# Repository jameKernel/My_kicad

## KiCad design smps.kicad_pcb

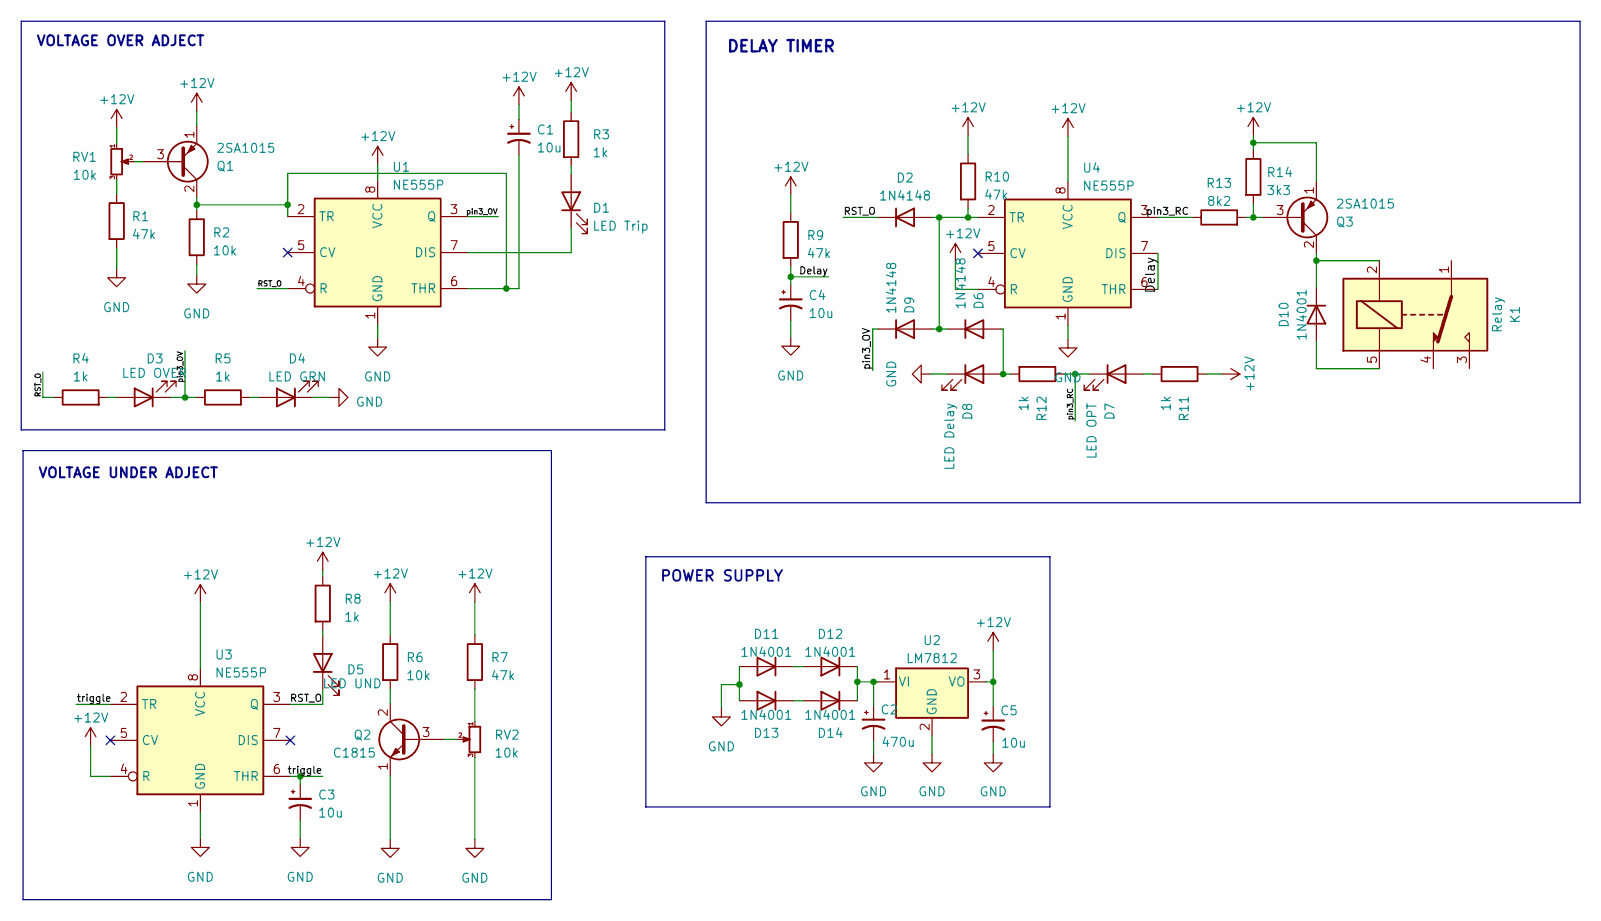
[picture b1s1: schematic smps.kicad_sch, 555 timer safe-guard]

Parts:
C1, C3, C5: 10u; CP_Radial_D4.0mm_P2.00mm
C2: 470u; CP_Radial_D6.3mm_P2.50mm
C4: 10u; CP_Radial_D6.3mm_P2.50mm
D1: LED Trip; LED_Rectangular_W5.0mm_H2.0mm
D2, D6, D9: 1N4148; D_DO-35_SOD27_P7.62mm_Horizontal
D3: LED OVER; LED_Rectangular_W5.0mm_H2.0mm
D4: LED GRN; LED_Rectangular_W5.0mm_H2.0mm
D5: LED UND; LED_Rectangular_W5.0mm_H2.0mm
D7: LED OPT; LED_Rectangular_W5.0mm_H2.0mm
D8: LED Delay; LED_Rectangular_W5.0mm_H2.0mm
D10, D11, D12, D13, D14: 1N4001; D_DO-41_SOD81_P10.16mm_Horizontal
K1: Relay; Relay_SPDT_SANYOU_SRD_Series_Form_C
Q1, Q3: 2SA1015; TO-92_Inline
Q2: C1815; TO-92_Inline
R1, R7, R9, R10: 47k; R_Axial_DIN0207_L6.3mm_D2.5mm_P10.16mm_Horizontal
R2, R6: 10k; R_Axial_DIN0207_L6.3mm_D2.5mm_P10.16mm_Horizontal
R3, R4, R5, R8, R11, R12: 1k; R_Axial_DIN0207_L6.3mm_D2.5mm_P10.16mm_Horizontal
R13: 8k2; R_Axial_DIN0207_L6.3mm_D2.5mm_P10.16mm_Horizontal
R14: 3k3; R_Axial_DIN0207_L6.3mm_D2.5mm_P10.16mm_Horizontal
RV1, RV2: 10k; Potentiometer_Vishay_T73YP_Vertical
U1, U3, U4: NE555P; DIP-8_W7.62mm
U2: LM7812; TO-220-3_Vertical

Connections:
+12V: C1.1, C5.1, Q1.1 (E), Q3.1 (E), R3.1, R6.1, R7.1, R8.1, R9.1, R10.1, R11.1, R14.1, RV1.1, U1.8 (VCC), U2.3 (VO), U3.4 (R), U3.8 (VCC), U4.4 (R), U4.8 (VCC)
/Delay: C4.1, R9.2, U4.6 (THR), U4.7 (DIS)
/RST_O: D2.1 (K), D5.1 (K), R4.1, U1.4 (R), U3.3 (Q)
/pin3_OV: D3.1 (K), D9.1 (K), R5.1, U1.3 (Q)
/pin3_RC: D7.1 (K), R12.1, R13.1, U4.3 (Q)
/triggle: C3.1, U3.2 (TR), U3.6 (THR)
GND: C2.2, C3.2, C4.2, C5.2, D4.1 (K), D8.1 (K), D11.2 (A), D13.2 (A), Q2.1 (E), R1.2, R2.2, RV2.3, U1.1 (GND), U2.2 (GND), U3.1 (GND), U4.1 (GND)
unnamed: D1.2 (A), R3.2
unnamed: D1.1 (K), U1.7 (DIS)
unnamed: D2.2 (A), D6.1 (K), D9.2 (A), R10.2, U4.2 (TR)
unnamed: D3.2 (A), R4.2
unnamed: D4.2 (A), R5.2
unnamed: D5.2 (A), R8.2
unnamed: D6.2 (A), D8.2 (A), R12.2
unnamed: D7.2 (A), R11.2
unnamed: D10.2 (A), K1.5
unnamed: D10.1 (K), K1.2, Q3.2 (C)
unnamed: D11.1 (K), D12.2 (A)
unnamed: C2.1, D12.1 (K), D14.1 (K), U2.1 (VI)
unnamed: D13.1 (K), D14.2 (A)
unnamed: Q1.3 (B), RV1.2
unnamed: C1.2, Q1.2 (C), R2.1, U1.2 (TR), U1.6 (THR)
unnamed: Q2.3 (B), RV2.2
unnamed: Q2.2 (C), R6.2
unnamed: Q3.3 (B), R13.2, R14.2
unnamed: R1.1, RV1.3
unnamed: R7.2, RV2.1

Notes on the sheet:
POWER SUPPLY
DELAY TIMER
VOLTAGE OVER ADJECT
VOLTAGE UNDER ADJECT

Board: 2 copper layers, 43 parts (0 on the bottom side), 27 nets, no tracks yet.

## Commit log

2022-11-01 after_schematic_drawing
